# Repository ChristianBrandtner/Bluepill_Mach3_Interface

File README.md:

# Bluepill_Mach3_Interface
Adapterboard to use cheap (7€) Mach3 CNC Breakout Board with Bluepill/Blackpill
You can find it at Aliexpress, search for  "MACH3 Engraving machine 5 Axis CNC Breakout Board With Optical Coupler" or similar.

I want to use it with 3 Axis millingmachine and grblHAL. https://github.com/terjeio/grblHAL

This is not tested, PCB is ordered
14.01.2021

new version V2, because 5V supply for MACH3 Interfaceboard are necessary.
Powersupply is now 12-24V for Bluepill_Mach3 Interface and MACH3 Interfaceboard.

18.01.2021

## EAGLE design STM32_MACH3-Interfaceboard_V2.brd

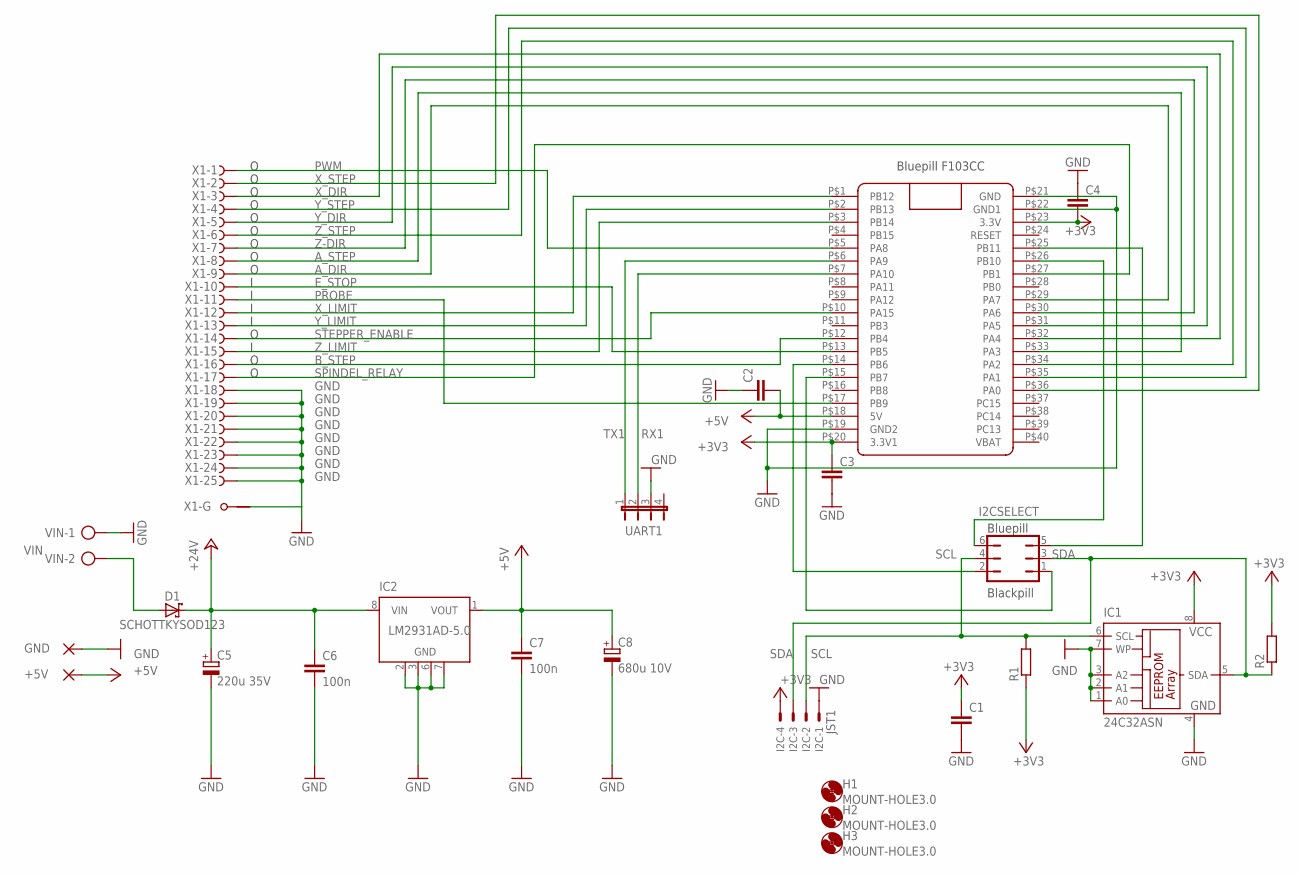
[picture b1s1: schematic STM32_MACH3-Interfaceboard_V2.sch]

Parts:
+5V: 2,54/1,0
C1, C2, C3, C4: C-EUC0805; C0805
C5: 220u 35V; PANASONIC_E7
C6, C7: 100n; C0805
C8: 680u 10V; PANASONIC_E7
D1: SCHOTTKYSOD123; SOD123
GND: 2,54/1,0
H1, H2, H3: MOUNT-HOLE3.0; 3,0
I2C: JST1; JST-XH-04-PACKAGE-LONG-PAD
I2CSELECT: JP3Q
IC1: 24C32ASN; SO-08
IC2: LM2931AD-5.0; SOIC8
R1, R2: R-EU_R0805; R0805
U$1: BLUE_PILL
UART1: JP4E; JP4
VIN: AK500/2
X1: F25HPS; F25HP

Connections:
+3V3: C1.1, C3.1, C4.2, I2C.4, IC1.8 (VCC), R1.1, R2.2, U$1.P$20 (3.3V1), U$1.P$23 (3.3V)
+5V: +5V.1, C2.2, C7.1, C8.+, IC2.1 (VOUT), U$1.P$18 (5V)
+24V: C5.+, C6.1, D1.C, IC2.8 (VIN)
A_DIR: U$1.P$29 (PA7), X1.9 (F)
A_STEP: U$1.P$33 (PA3), X1.8 (F)
B_STEP: U$1.P$12 (PB4), X1.16 (F)
E_STOP: U$1.P$13 (PB5), X1.10 (F)
GND: C1.2, C2.1, C3.2, C4.1, C5.-, C6.2, C7.2, C8.-, GND.1, I2C.1, IC1.1 (A0), IC1.2 (A1), IC1.3 (A2), IC1.4 (GND), IC1.7 (WP), IC2.2 (GND), IC2.3 (GND), IC2.6 (GND), IC2.7 (GND), U$1.P$19 (GND2), U$1.P$21 (GND), U$1.P$22 (GND1), UART1.3, VIN.1, X1.18 (F), X1.19 (F), X1.20 (F), X1.21 (F), X1.22 (F), X1.23 (F), X1.24 (F), X1.25 (F), X1.G1
unnamed: I2CSELECT.5, U$1.P$25 (PB11)
unnamed: I2CSELECT.6, U$1.P$26 (PB10)
unnamed: I2CSELECT.2, U$1.P$14 (PB6)
unnamed: I2CSELECT.1, U$1.P$15 (PB7)
PROBE: U$1.P$17 (PB9), X1.11 (F)
PWM: U$1.P$5 (PA8), X1.1 (F)
RX1: U$1.P$7 (PA10), UART1.2
SCL: I2C.2, I2CSELECT.4, IC1.6 (SCL), R1.2
SDA: I2C.3, I2CSELECT.3, IC1.5 (SDA), R2.1
SPINDEL_RELAY: U$1.P$27 (PB1), X1.17 (F)
STEPPER_ENABLE: U$1.P$10 (PA15), X1.14 (F)
TX1: U$1.P$6 (PA9), UART1.1
VIN: D1.A, VIN.2
X_DIR: U$1.P$32 (PA4), X1.3 (F)
X_LIMIT: U$1.P$1 (PB12), X1.12 (F)
X_STEP: U$1.P$36 (PA0), X1.2 (F)
Y_DIR: U$1.P$31 (PA5), X1.5 (F)
Y_LIMIT: U$1.P$2 (PB13), X1.13 (F)
Y_STEP: U$1.P$35 (PA1), X1.4 (F)
Z-DIR: U$1.P$30 (PA6), X1.7 (F)
Z_LIMIT: U$1.P$3 (PB14), X1.15 (F)
Z_STEP: U$1.P$34 (PA2), X1.6 (F)

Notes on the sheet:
Bluepill F103CC
Bluepill
Blackpill

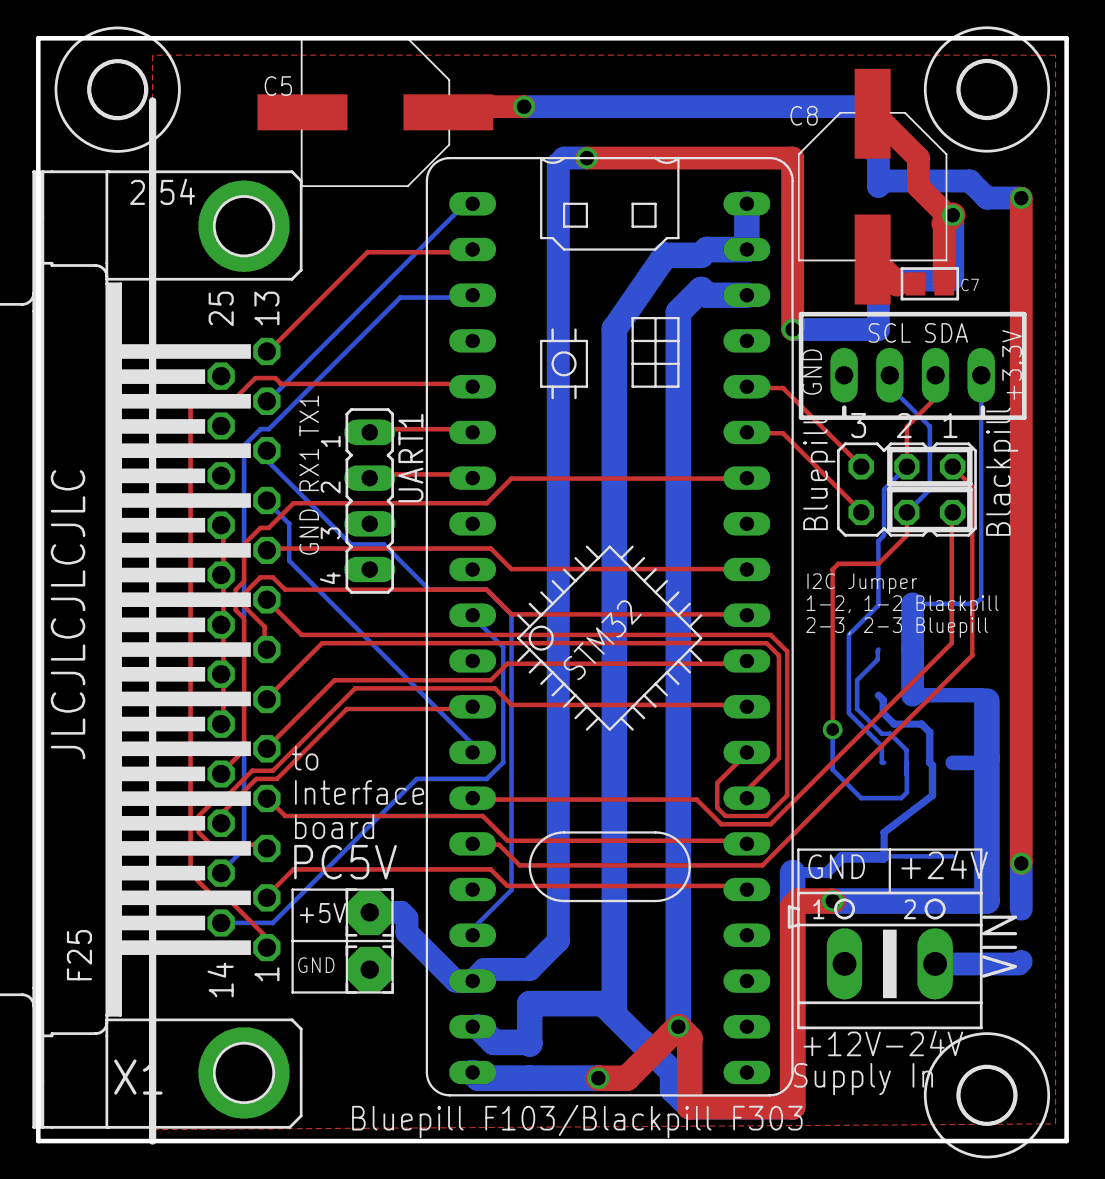
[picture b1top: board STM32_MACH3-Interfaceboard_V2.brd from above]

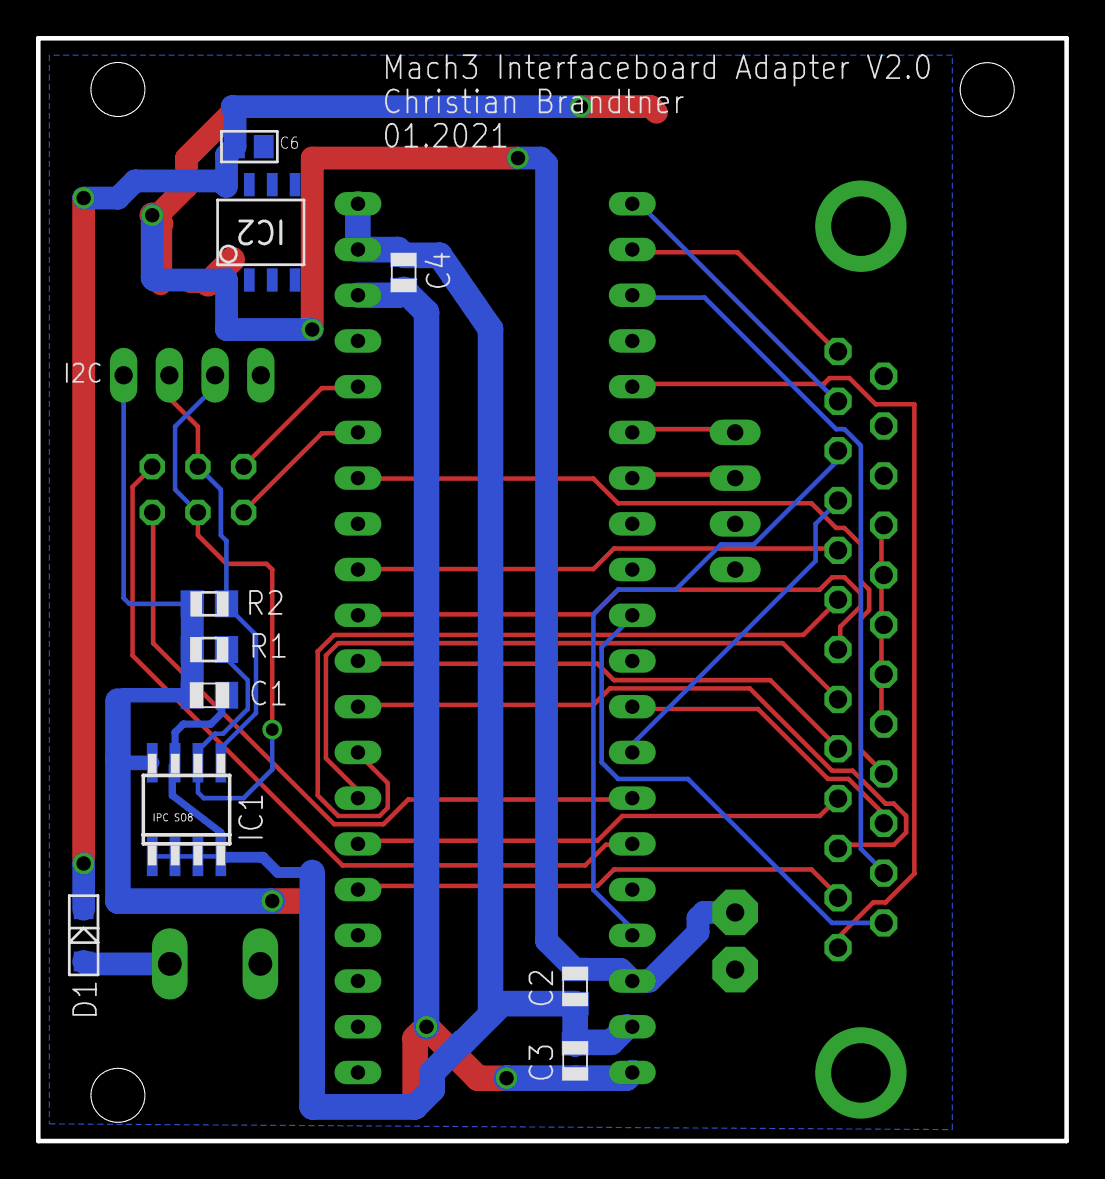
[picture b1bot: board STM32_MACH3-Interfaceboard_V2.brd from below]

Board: 2 copper layers, 57.1 x 61.3 mm, 24 parts (10 on the bottom side), 30 nets.

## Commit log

2021-01-18 Add files via upload
    New version, includes now 5V supply for the MACH3 Interface board
